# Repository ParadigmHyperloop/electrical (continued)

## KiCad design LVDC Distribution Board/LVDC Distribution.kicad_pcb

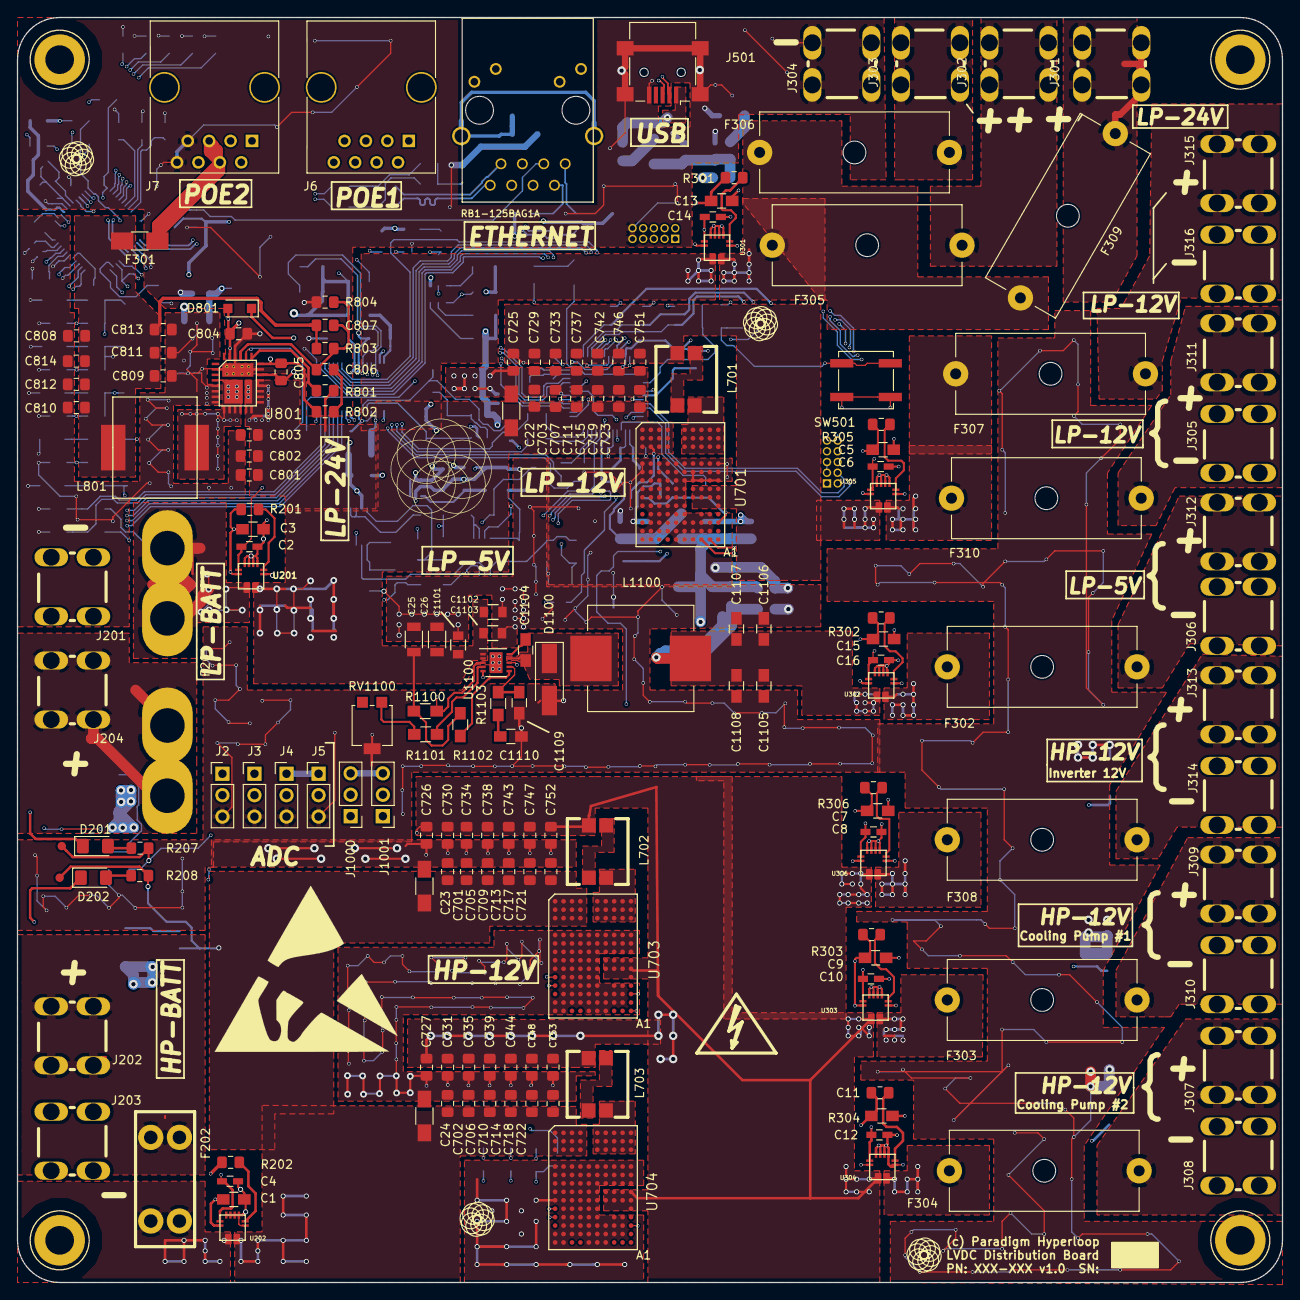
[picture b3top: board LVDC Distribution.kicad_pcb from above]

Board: 4 copper layers, 150.0 x 150.0 mm, 370 parts (0 on the bottom side), 204 nets.

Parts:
C1, C3, C5, C7, C9, C11, C13, C15, C17: 0.1uF; C_0805_HandSoldering
C2, C4, C6, C8, C10, C12, C14, C16: 1nF; C_0603_HandSoldering
C18: 0.1uF; SMD_pkg_0805
C19, C20: 15pF; SMD_pkg_0603
C21: 0.1u; C_0603
C22, C23, C24: 100uF; C_1206_HandSoldering
C25, C26: 10u; SMD_pkg_1206
C27, C709, C710, C711, C713, C714, C715, C717, C718, C719, C721, C722, C723: 4.7uF; C_0805_2012Metric_Pad1.15x1.40mm_HandSolder
C28: 1u; C_0402
C29: 10nF; R_0402
C31, C32, C33, C34, C35, C36: 0.1uF; R_0402
C37, C602: 18pF; R_0402
C501, C504, C506, C609, C801, C808: 10uF; C_0805_2012Metric_Pad1.15x1.40mm_HandSolder
C502, C503, C507, C751, C752, C753, C805, C806: 0.1uF; C_0805_2012Metric_Pad1.15x1.40mm_HandSolder
C505, C510, C741, C742, C743, C744, C746, C747, C748, C750: 1uF; C_0805_2012Metric_Pad1.15x1.40mm_HandSolder
C508, C509: 22pF; SMD_pkg_0603
C605, C606: 6.8nF; C_0805_2012Metric_Pad1.15x1.40mm_HandSolder
C607: 10nF; C_0805_2012Metric_Pad1.15x1.40mm_HandSolder
C608: 100nF; C_0805_2012Metric_Pad1.15x1.40mm_HandSolder
C701, C702, C703, C705, C706, C707, C725, C726, C727, C729, C730, C731, C733, C734, C735, C737, C738, C739, C809, C810, C811, C812, C813, C814: 22uF; C_0805_2012Metric_Pad1.15x1.40mm_HandSolder
C802, C803, C804: 2.2uF; C_0805_2012Metric_Pad1.15x1.40mm_HandSolder
C807: 4.7nF; C_0805_2012Metric_Pad1.15x1.40mm_HandSolder
C900, C903, C904, C906, C907, C1001, C1004: 1u; C_0805_HandSoldering
C901, C1000, C1002, C1003, C1005, C1108: 0.1u; C_0805_HandSoldering
C902, C905: 10u; C_0805_HandSoldering
C908: 150p; C_0805_HandSoldering
C1101: 10u; SMD_pkg_0805
C1102: 0.1u; SMD_pkg_0805
C1103: 10n; SMD_pkg_0805
C1104: 47n; C_0805_HandSoldering
C1105, C1106: 22u; C_0805_HandSoldering
C1107: 18u; C_0805_HandSoldering
C1109: 22p; C_0805_HandSoldering
C1110: 1500p; C_0805_HandSoldering
D201, D202, D701, D702, D703, D704, D705: BLUE; LED_1206_3216Metric_Pad1.42x1.75mm_HandSolder
D501, D502: GREEN; LED_1206_3216Metric_Pad1.42x1.75mm_HandSolder
D801: D_Schottky; D_SOD-123F
D1100: 2A/40V; D_SMA_Handsoldering
F201: 40A; FUSE_MAXI_36-3555-2-ND
F202: 25A; FUSE_MINI_36-3568-ND
F301: 2A; Fuse_SMD1206_HandSoldering
F302: 1A; Fuseholder5x20_horiz_open_Schurter_0031_8201
F303, F304, F307, F308: 3A; Fuseholder5x20_horiz_open_Schurter_0031_8201
F305, F306, F309: 8A; Fuseholder5x20_horiz_open_Schurter_0031_8201
F310: 2A; Fuseholder5x20_horiz_open_Schurter_0031_8201
F501: 500mA; SMD_pkg_0805
H1, H2, H3, H4: Mount; 3.4mm_mounting_hole_SILK
J1: EXT_SPI; PinHeader_2x05_P1.27mm_Vertical
J2, J3, J4, J5: ADC_IN1; PinHeader_1x03_P2.54mm_Vertical
J6, J7: RJ45_LED; RJ45_8
J201: BAT_LP_IN-; LVDC_M3_Lug
J202: BAT_HP_IN+; LVDC_M3_Lug
J203: BAT_HP_IN-; LVDC_M3_Lug
J204: BAT_LP_IN+; LVDC_M3_Lug
J301, J302, J303, J304, J305, J306, J307, J308, J309, J310, J311, J312, J313, J314, J315, J316: Lug Terminal; LVDC_M3_Lug
J501: USB_B_Mini; USB_Mini-B_Lumberg_2486_01_Horizontal
J502: Conn_02x05_Odd_Even; PinHeader_2x05_P1.27mm_Vertical
J601: RB1-125BAG1A; WIZNET_RB1-125BAG1A
J1000, J1001: Conn_01x03_Female; PinHeader_1x03_P2.54mm_Vertical
JP701: Jumper; R_0805_2012Metric_Pad1.15x1.40mm_HandSolder
L501, L502: Ferrite_Bead; R_1206_3216Metric_Pad1.42x1.75mm_HandSolder
L601, L602: Ferrite_Bead_Small; R_1206_3216Metric_Pad1.42x1.75mm_HandSolder
L701, L702, L703: FPT705-230-R; Inductor_Dual_Eaton
L801: 47uH; Wurth_Inductor_47uH
L900, L901: Ferrite_Bead; L_0805_HandSoldering
L1100: 22u; L_Wuerth_WE-PD-Typ-LS_Handsoldering
Q201, Q202: Q_NMOS_GDS; TO-252-2
Q301, Q302, Q303: NMOS_GDS; TO-252-2
R1: 330; SMD_pkg_0805
R5, R1001, R1002, R1004: 150; R_0805_HandSoldering
R7, R8, R9, R10: 0; SMD_pkg_0805
R11, R13: 10k; C_0603
R12: 100k; C_0603
R14, R16, R907, R1003, R1006: 0; R_0805_HandSoldering
R18: 10K; R_0402
R23: 1M; R_0402
R43, R44, R45, R46: 0; C_0603
R201, R202, R301, R302, R303, R304, R305, R306, R804: 1k; R_0805_2012Metric_Pad1.15x1.40mm_HandSolder
R203, R205, R707, R709, R711, R713: 900k; R_0805_2012Metric_Pad1.15x1.40mm_HandSolder
R204, R206, R801: 100k; R_0805_2012Metric_Pad1.15x1.40mm_HandSolder
R207, R208: 2k; R_0805_2012Metric_Pad1.15x1.40mm_HandSolder
R209, R211: 700k; R_0805_2012Metric_Pad1.15x1.40mm_HandSolder
R210, R212: 500k; R_0805_2012Metric_Pad1.15x1.40mm_HandSolder
R501, R603, R604: 330; R_0805_2012Metric_Pad1.15x1.40mm_HandSolder
R502, R803: 10k; R_0805_2012Metric_Pad1.15x1.40mm_HandSolder
R503, R504, R505: 100k; SMD_pkg_0805
R506: 680; R_0805_2012Metric_Pad1.15x1.40mm_HandSolder
R606: 0; R_0805_2012Metric_Pad1.15x1.40mm_HandSolder
R607, R608, R611, R612, R613, R614, R615, R624, R625, R626: 10K; R_0805_2012Metric_Pad1.15x1.40mm_HandSolder
R609, R610, R616, R619: 49.9; R_0805_2012Metric_Pad1.15x1.40mm_HandSolder
R617, R618, R620, R621: 33; R_0805_2012Metric_Pad1.15x1.40mm_HandSolder
R622: 10; R_0805_2012Metric_Pad1.15x1.40mm_HandSolder
R623: 12.4K; R_0805_2012Metric_Pad1.15x1.40mm_HandSolder
R701: 2.5k; R_0805_HandSoldering
R702, R705: 4.7k; R_0805_2012Metric_Pad1.15x1.40mm_HandSolder
R703: 58; R_0805_2012Metric_Pad1.15x1.40mm_HandSolder
R704: 9.2k; R_0805_2012Metric_Pad1.15x1.40mm_HandSolder
R706: 11k; R_0805_2012Metric_Pad1.15x1.40mm_HandSolder
R708, R714: 250k; R_0805_2012Metric_Pad1.15x1.40mm_HandSolder
R710: 620k; R_0805_2012Metric_Pad1.15x1.40mm_HandSolder
R712: 120k; R_0805_2012Metric_Pad1.15x1.40mm_HandSolder
R802: 133k; R_0805_2012Metric_Pad1.15x1.40mm_HandSolder
R900, R909, R910, R1100, R1101, R1102: 10k; R_0805_HandSoldering
R901, R902, R903: 100k; R_0805_HandSoldering
R904: 45k; R_0805_HandSoldering
R905: 5k; R_0805_HandSoldering
R906: 50k; R_0805_HandSoldering
R908: 100; R_0805_HandSoldering
R1000, R1007: 1M; R_0805_HandSoldering
R1103: 24.9k; R_0805_HandSoldering
RV1: R_POT; Potentiometer_Bourns_3314G_Vertical
RV1100: 100k; Potentiometer_Bourns_3314G_Vertical
SW501: SW_Push; SW_SPST_B3SL-1022P
TP1, TP2, TP3, TP4, TP5, TP6, TP7, TP601, TP604, TP605, TP606, TP607, TP608: Conn_01x01; Testpoint_circle_0.5mm
U1: W5500; LQFP-48_7x7mm_Pitch0.5mm
U201, U202, U301, U302, U303, U304, U305, U306: ACS711
U501: ATSAMD21G18A-MFT; TQFP-48_7x7mm_Pitch0.5mm
U701, U703, U704: PI3303-00-LGIZ; PI330X
U705: AZ1117-3.3; SOT-223-3_TabPin2
U801: MIC28510; MIC28510_QFN
U900: LM3880; SOT-23-6
U901: LM4132; SOT-23-5_HandSoldering
U902: ADS7953; TSSOP-38_4.4x9.7mm_Pitch0.5mm
U903: LMV601; SOT-363_SC-70-6
U904: OPA192; SOT-23-5_HandSoldering
U1000, U1001: AD849X; MSOP-8_3x3mm_Pitch0.65mm
U1100: A8591; DFN-10-1EP_3x3mm_Pitch0.5mm
Y1, Y601: 25MHz; Murata_25MHz_XTAL_XRCGB25M000F3M00R0
Y501: 32.7680kHz; Crystal_SMD_EuroQuartz_EQ161-2Pin_3.2x1.5mm_HandSoldering
lo1, lo1#2: Serial Block; SN_BLOCK
lo2, lo4, lo8: Logo; ParadigmLogo_0_5x0_5
lo3, lo3#2, lo10, lo11, lo12, lo13: Logo; Paradigm_Logo_Very_Small
lo5: Logo; Symbol_HighVoltage_Type2_SilkTop_VerySmall
lo6: Logo; KiCad-Logo_40mm_SilkScreen
lo7, lo9: Logo; ESD-Logo_22x20mm_SilkScreen

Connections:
3V3A_W5500: C31.1, C32.1, C33.1, C34.1, C35.1, C36.1, C609.1, J601.L1, J601.L3, L602.2, R606.2, R607.2, R608.2, R609.1, R610.1, R622.2, TP608.1, U1.28, U1.32, U1.35, U1.39, U1.41, U1.45
3V3_FILT: C506.1, C507.1, L502.1, U501.6
+3V3: C1.1, C3.1, C5.1, C7.1, C9.1, C11.1, C13.1, C15.1, C501.1, C502.1, C503.1, C750.1, C905.1, J502.1, L502.2, L602.1, L901.2, R201.2, R202.2, R301.2, R302.2, R303.2, R304.2, R305.2, R306.2, R502.1, R506.2, R703.2, R909.2, R910.2, TP3.1, U201.12, U202.12, U301.12, U302.12, U303.12, U304.12, U305.12, U306.12, U501.17, U501.36, U501.44, U705.2
+5V: C28.1, C741.1, C804.1, C900.1, C902.1, C907.2, C1105.1, C1106.1, C1107.1, C1108.1, D801.2, J1.1, J1.2, J2.1, J3.1, J4.1, J5.1, J1000.3, J1001.3, JP701.2, L900.2, L1100.2, R704.1, R709.1, R900.1, R901.1, R902.1, R903.1, R904.1, R906.2, TP2.1, U302.1, U705.3, U801.1, U900.1, U901.4, U903.5, U903.6, U904.5, U1000.7, U1001.7, U1100.5
/Inputs and Fusing/HP_Vin+: C23.1, C24.1, C701.1, C702.1, C705.1, C706.1, C709.1, C710.1, C713.1, C714.1, C717.1, C718.1, C721.1, C722.1, R208.2, R209.1, TP7.1, U202.3, U703.1, U704.1
/Inputs and Fusing/LP_Vin+: C22.1, C25.1, C26.1, C703.1, C707.1, C711.1, C715.1, C719.1, C723.1, C801.1, C802.1, C803.1, C1101.1, C1102.1, C1103.1, R11.1, R207.2, R211.1, R801.1, R1100.1, R1102.1, TP6.1, U201.3, U301.1, U701.1, U801.4, U1100.1, U1100.2
/Power Conversion/5V_Converter/COMP: C1109.1, R1103.1, U1100.7
/Power Conversion/HP12V: C726.1, C727.1, C730.1, C731.1, C734.1, C735.1, C738.1, C739.1, C743.1, C744.1, C747.1, C748.1, C752.1, C753.1, L702.3, L703.3, R705.1, R713.1, TP5.1, U303.1, U304.1, U306.1, U703.11, U703.12, U704.11, U704.12
/Power Conversion/LP12V: C725.1, C729.1, C733.1, C737.1, C742.1, C746.1, C751.1, L701.3, R702.1, R707.1, TP1.1, U305.1, U701.11, U701.12
/Power Conversion/LP24V: C807.2, C808.1, C809.1, C810.1, C811.1, C812.1, C813.1, C814.1, F301.2, L801.2, R706.1, R711.1, R803.2, TP4.1
/Power Conversion/USB5V: C504.1, C505.1, JP701.1, L501.1, R501.1
/Power Outputs/NAP_PoE/NAP_Vin+: F301.1, J7.4, J7.5
/Power Outputs/NAP_PoE/RX+: J6.1, J7.1
/Power Outputs/NAP_PoE/RX-: J6.2, J7.2
/Power Outputs/NAP_PoE/TX+: J6.3, J7.3
/Power Outputs/NAP_PoE/TX-: J6.6, J7.6
/SAMD21uC/ADC_CS: R7.1, U501.9
/SAMD21uC/ADC_SCLK: R8.1, U501.10
/SAMD21uC/ADC_SDI: R9.1, U501.11
/SAMD21uC/ADC_SDO: R10.1, U501.12
/SAMD21uC/ADC_Sensors/2V5_VREF: C901.1, U901.5
/SAMD21uC/ADC_Sensors/3V3_EN: R902.2, U900.5
/SAMD21uC/ADC_Sensors/3V3_FILT: C906.1, L901.1, U902.36
/SAMD21uC/ADC_Sensors/5V_FILT: C903.1, C904.1, L900.1, U902.5, U902.29
/SAMD21uC/ADC_Sensors/AINP: C908.1, R908.1, U902.8
/SAMD21uC/ADC_Sensors/MXO: R906.1, R907.2, U902.7, U904.3
/SAMD21uC/ADC_Sensors/TC_VREF: U903.3, U903.4
/SAMD21uC/ADC_Sensors/Thermocouple/OUT1: R1003.1, U1000.5, U1000.6
/SAMD21uC/ADC_Sensors/Thermocouple/OUT2: R1006.1, U1001.5, U1001.6
/SAMD21uC/ADC_Sensors/Thermocouple/TC_VREF: U1000.2, U1001.2
/SAMD21uC/ADC_Sensors/VREF_EN: R903.2, U900.4, U901.3
/SAMD21uC/AIN_0: J2.2, U501.8
/SAMD21uC/AIN_1: J3.2, U501.7
/SAMD21uC/AIN_2: J4.2, U501.48
/SAMD21uC/AIN_3: J5.2, U501.47
/SAMD21uC/EXT_SPI_CS0: J1.4, U501.13
/SAMD21uC/EXT_SPI_CS1: J1.6, U501.14
/SAMD21uC/EXT_SPI_SCLK: J1.7, U501.30
/SAMD21uC/EXT_SPI_SDI: J1.3, U501.28
/SAMD21uC/EXT_SPI_SDO: J1.5, U501.29
/SAMD21uC/~RESET: C18.1, R1.1, U501.40
/Wiznet Ethernet/1V2_VBG_NC: TP607.1, U1.42
/Wiznet Ethernet/1V20: C29.1, U1.46
/Wiznet Ethernet/3V3D_W5500: R606.1, U1.4
/Wiznet Ethernet/ACT_LED: R604.2, U1.3
/Wiznet Ethernet/ACT_LED_R: J601.L4, R604.1
/Wiznet Ethernet/DUP_LED_NC: TP601.1, U1.2
/Wiznet Ethernet/LINK_LED: R603.1, U1.1
/Wiznet Ethernet/LINK_LED_R: J601.L2, R603.2
/Wiznet Ethernet/PMODE0: R624.2, U1.21
/Wiznet Ethernet/PMODE1: R625.2, U1.20
/Wiznet Ethernet/PMODE2: R626.2, U1.19
/Wiznet Ethernet/REF_CAP: C27.1, U1.44
/Wiznet Ethernet/REF_RES: R623.2, U1.34
/Wiznet Ethernet/RSVD0: R18.2, U1.47
/Wiznet Ethernet/RSVD1: R611.1, U1.14
/Wiznet Ethernet/RSVD2: R612.1, U1.15
/Wiznet Ethernet/RSVD3: R613.1, U1.16
/Wiznet Ethernet/RSVD4: R614.1, U1.17
/Wiznet Ethernet/RSVD5: R615.1, U1.18
/Wiznet Ethernet/RX_C_N: C606.2, J601.R8
/Wiznet Ethernet/RX_C_P: C605.2, J601.R7
/Wiznet Ethernet/RX_N: R621.2, U1.29
/Wiznet Ethernet/RX_P: R620.2, U1.30
/Wiznet Ethernet/SPD_LED_NC: TP606.1, U1.48
/Wiznet Ethernet/TCT_RCT: C608.1, J601.R3, R622.1
/Wiznet Ethernet/TX_N: R618.2, U1.25
/Wiznet Ethernet/TX_P: R617.2, U1.26
/Wiznet Ethernet/TX_R_N: J601.R2, R610.2, R618.1
/Wiznet Ethernet/TX_R_P: J601.R1, R609.2, R617.1
/Wiznet Ethernet/XTAL_IN: C37.2, R23.2, U1.6, Y601.2
/Wiznet Ethernet/XTAL_OUT: C602.2, R23.1, U1.7, Y601.1
ADC_S0_BUS: R7.2, R909.1, U902.31
ADC_S1_BUS: R8.2, U902.32
ADC_S2_BUS: R9.2, U902.33
ADC_S3_BUS: R10.2, R910.1, U902.34
COOL_PUMP_CTRL_1: Q303.1, R504.1, U501.26
COOL_PUMP_CTRL_2: Q301.1, R503.1, U501.27
CoolingP1_Current: C10.1, U303.11, U902.25
CoolingP2_Current: C12.1, U304.11, U902.26
GND: C1.2, C2.2, C3.2, C4.2, C5.2, C6.2, C7.2, C8.2, C9.2, C10.2, C11.2, C12.2, C13.2, C14.2, C15.2, C16.2, C17.2, C18.2, C19.1, C20.1, C21.2, C22.2, C23.2, C24.2, C25.2, C26.2, C27.2, C28.2, C29.2, C31.2, C32.2, C33.2, C34.2, C35.2, C36.2, C37.1, C501.2, C502.2, C503.2, C504.2, C505.2, C506.2, C507.2, C508.2, C509.2, C510.2, C602.1, C607.2, C608.2, C609.2, C701.2, C702.2, C703.2, C705.2, C706.2, C707.2, C709.2, C710.2, C711.2, C713.2, C714.2, C715.2, C717.2, C718.2, C719.2, C721.2, C722.2, C723.2, C725.2, C726.2, C727.2, C729.2, C730.2, C731.2, C733.2, C734.2, C735.2, C737.2, C738.2, C739.2, C741.2, C742.2, C743.2, C744.2, C746.2, C747.2, C748.2, C750.2, C751.2, C752.2, C753.2, C801.2, C802.2, C803.2, C804.2, C808.2, C809.2, C810.2, C811.2, C812.2, C813.2, C814.2, C900.2, C901.2, C902.2, C903.2, C904.2, C905.2, C906.2, C907.1, C908.2, C1000.1, C1002.2, C1003.1, C1005.2, C1101.2, C1102.2, C1103.2, C1105.2, C1106.2, C1107.2, C1108.2, C1109.2, C1110.2, D501.1, D701.1, D702.1, D703.1, D704.1, D705.1, D1100.2, J1.9, J1.10, J2.3, J3.3, J4.3, J5.3, J7.7, J7.8, J304.1, J306.1, J312.1, J316.1, J501.5, J501.6, J502.3, J502.5, L601.1, Q201.3, Q202.3, Q301.3, Q302.3, Q303.3, R13.2, R18.1, R204.2, R206.2, R210.1, R212.1, R503.2, R504.2, R505.2, R611.2, R612.2, R613.2, R614.2, R615.2, R623.1, R624.1, R625.1, R626.1, R708.2, R710.2, R712.2, R714.2, R804.2, R905.2, R1000.2, R1007.2, RV1.2, RV1100.2, SW501.1, U1.5, U1.24, U1.27, U1.33, U1.38, U1.40, U1.43, U201.5, U201.7, U202.5, U202.7, U301.5, U301.7, U302.5, U302.7, U303.5, U303.7, U304.5, U304.7, U305.5, U305.7, U306.5, U306.7, U501.5, U501.18, U501.35, U501.42, U701.3, U701.6, U701.7, U703.6, U703.7, U704.6, U704.7, U705.1, U801.2, U801.5, U900.2, U901.2, U902.3, U902.6, U902.9, U902.10, U902.19, U902.20, U902.30, U902.35, U903.2, U904.2, U1000.3, U1001.3, U1100.8
HP12V_EN: R44.2, U501.19
HP12V_VSense: R713.2, R714.1, U902.13
HPBAT_VSense: R205.2, R206.1, U902.17
HPBAT_Voltage: F202.1, R205.1, U202.1
HPBatt_Current: C4.1, U202.11, U902.11
INVERTER_CTRL: Q302.1, R505.1, U501.25
Inverter12V_Current: C8.1, U306.11, U902.22
LP5V_EN: R46.2, U501.4
LP5V_Output_Current: C16.1, U302.11, U902.24
LP5V_VSense: R709.2, R710.1, U902.16
LP12V_EN: R43.2, U501.3
LP12V_Output_Current: C6.1, U305.11, U902.21
LP12V_VSense: R707.2, R708.1, U902.15
LP24V_EN: R45.2, U501.20
LP24V_VSense: R711.2, R712.1, U902.14
LPBAT_VSense: R203.2, R204.1, U902.18
LPBAT_Voltage: F201.1, R203.1, U201.1
LPBatt_Current: C2.1, U201.11, U902.12
NETW_CS: U1.8, U501.21
NETW_INT_L: R608.1, TP605.1, U1.12, U501.31
NETW_MISO: U1.10, U501.22
NETW_MOSI: U1.11, U501.15
NETW_RESET_L: R607.1, TP604.1, U1.13, U501.32
NETW_SCLK: U1.9, U501.16
unnamed: C17.1, C510.1, U501.43
unnamed: C19.2, U501.23, Y1.2
unnamed: C20.2, U501.24, Y1.1
unnamed: C21.1, U701.8
unnamed: C508.1, U501.1, Y501.1
unnamed: C509.1, U501.2, Y501.2
unnamed: C605.1, R619.1, R620.1
unnamed: C606.1, R616.1, R621.1
unnamed: C607.1, R616.2, R619.2
unnamed: C805.1, L801.1, R802.2, U801.8, U801.9
unnamed: C805.2, D801.1, U801.7
unnamed: C806.1, C807.1, R803.1, R804.1, U801.10
unnamed: C806.2, R802.1
unnamed: C1000.2, C1001.1, R1001.1, U1000.1
unnamed: C1001.2, C1002.1, R1002.1, U1000.8
unnamed: C1003.2, C1004.1, R1004.1, U1001.1
unnamed: C1004.2, C1005.1, R5.1, U1001.8
unnamed: C1104.1, D1100.1, L1100.1, U1100.9
unnamed: C1104.2, U1100.10
unnamed: C1110.1, R1103.2
unnamed: D201.1, J201.1, Q202.2
unnamed: D201.2, R207.1
unnamed: D202.1, J203.1, Q201.2
unnamed: D202.2, R208.1
unnamed: D501.2, R501.2
unnamed: D502.1, U501.38
unnamed: D502.2, R506.1
unnamed: D701.2, R702.2
unnamed: D702.2, R703.1
unnamed: D703.2, R704.2
unnamed: D704.2, R705.2
unnamed: D705.2, R706.2
unnamed: F201.2, J204.1
unnamed: F202.2, J202.1
unnamed: F302.1, J305.1
unnamed: F302.2, U302.3
unnamed: F303.1, J309.1
unnamed: F303.2, U303.3
unnamed: F304.1, J307.1
unnamed: F304.2, U304.3
unnamed: F305.1, J302.1
unnamed: F305.2, F306.2, F309.2, U301.3
unnamed: F306.1, J303.1
unnamed: F307.1, J315.1
unnamed: F307.2, F310.2, U305.3
unnamed: F308.1, J313.1
unnamed: F308.2, U306.3
unnamed: F309.1, J301.1
unnamed: F310.1, J311.1
unnamed: F501.1, L501.2
unnamed: F501.2, J501.1
unnamed: J308.1, Q301.2
unnamed: J310.1, Q303.2
unnamed: J314.1, Q302.2
unnamed: J601.SH, L601.2
unnamed: J1000.1, R1002.2, R1003.2
unnamed: J1000.2, R1000.1, R1001.2
unnamed: J1001.1, R5.2, R1006.2
unnamed: J1001.2, R1004.2, R1007.1
unnamed: L701.1, U701.13
unnamed: L701.2, L701.4
unnamed: L702.1, U703.13
unnamed: L702.2, L702.4
unnamed: L703.1, U704.13
unnamed: L703.2, L703.4
unnamed: Q201.1, R209.2, R210.2
unnamed: Q202.1, R211.2, R212.2
unnamed: R11.2, R13.1, R43.1, U701.5
unnamed: R12.2, RV1.3, U701.9
unnamed: R14.1, U703.2
unnamed: R14.2, U704.3
unnamed: R16.1, U703.5
unnamed: R16.2, R44.1, U704.5
unnamed: R45.1, U801.6
unnamed: R201.1, U201.6
unnamed: R202.1, U202.6
unnamed: R301.1, U301.6
unnamed: R302.1, U302.6
unnamed: R303.1, U303.6
unnamed: R304.1, U304.6
unnamed: R305.1, U305.6
unnamed: R306.1, U306.6
unnamed: R701.1, U703.3, U703.4
unnamed: R701.2, U704.2
unnamed: R801.2, U801.3
unnamed: R900.2, U900.3
unnamed: R901.2, U900.6
unnamed: R904.2, R905.1, U903.1
unnamed: R907.1, R908.2, U904.1, U904.4
unnamed: R46.1, R1100.2, U1100.3
unnamed: R1101.1, U1100.4
unnamed: R1101.2, RV1100.1
unnamed: R1102.2, U1100.6
Nodes_Current: C14.1, U301.11, U902.23
SWCLK: J502.4, U501.45
SWDIO: J502.2, U501.46
USB+: J501.3, U501.34
USB-: J501.2, U501.33
~RESET~: J502.10, R1.2, R502.2, SW501.2

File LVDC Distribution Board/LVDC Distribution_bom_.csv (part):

Component,Description,Part,References,Value,Footprint,Quantity Per PCB,Datasheet,Mfg. Part Num,Package,Mfg. Name,MP,Tolerance,Vendor Part Num,Category,Status,Family,MPN,Digi-Key_PN,DK_Datasheet_Link,DK_Detail_Page,Manufacturer
1,"Unpolarized capacitor, small symbol",C_Small,C21 C1102,0.1u,,2,~,,,,,,,,,,,,,,
2,Unpolarized capacitor,C,C1 C3 C5 C7 C9 C11 C15 C901 C1000 C1002 C1003 C1005 C1108,0.1uF,C_0805_HandSoldering,13,~,,,,,,,,,,,,,,
3,Unpolarized capacitor,C,C13 C17 C18 C502 C503 C507 C608 C610 C611 C612 C613 C614 C615 C751 C752 C753 C805 C806,0.1uF,C_0805_2012Metric_Pad1.15x1.40mm_HandSolder,18,~,,,,,,,,,,,,,,
4,Unpolarized capacitor,C,C22 C23 C24,100uF,C_1206_HandSoldering,3,445-11739-1-ND,,,,,,,,,,,,,,
5,"Unpolarized capacitor, small symbol",C_Small,C1103,10n,,1,~,,,,,,,,,,,,,,
6,Unpolarized capacitor,C,C604 C607,10nF,C_0805_2012Metric_Pad1.15x1.40mm_HandSolder,2,,,,,,,,,,,,,,,
7,"Unpolarized capacitor, small symbol",C_Small,C1101,10u,,1,~,,,,,,,,,,,,,,
8,Unpolarized capacitor,C,C902 C905,10u,C_0805_HandSoldering,2,~,,,,,,,,,,,,,,
9,Unpolarized capacitor,C,C501 C504 C506 C609 C801 C808,10uF,C_0805_2012Metric_Pad1.15x1.40mm_HandSolder,6,~,,,,,,,,,,,,,,
10,"Unpolarized capacitor, small symbol",C_Small,C1110,1500p,C_0805_HandSoldering,1,~,,,,,,,,,,,,,,
11,Unpolarized capacitor,C,C908,150p,C_0805_HandSoldering,1,~,,,,,,,,,,,,,,
12,Unpolarized capacitor,C,C19 C20,15pF,C_0805_2012Metric_Pad1.15x1.40mm_HandSolder,2,~,,,,,,,,,,,,,,
13,Unpolarized capacitor,C,C601 C602,18pF,C_0805_2012Metric_Pad1.15x1.40mm_HandSolder,2,,,,,,,,,,,,,,,
14,"Unpolarized capacitor, small symbol",C_Small,C1107,18u,C_0805_HandSoldering,1,~,,,,,,,,,,,,,,
15,Unpolarized capacitor,C,C2 C4 C6 C8 C10 C12 C14 C16,1nF,C_0603_HandSoldering,8,~,,,,,,,,,,,,,,
16,Unpolarized capacitor,C,C900 C903 C904 C906 C907 C1001 C1004,1u,C_0805_HandSoldering,7,~,,,,,,,,,,,,,,
17,Unpolarized capacitor,C,C505 C510 C741 C742 C743 C744 C746 C747 C748 C750,1uF,C_0805_2012Metric_Pad1.15x1.40mm_HandSolder,10,~,,,,,,,,,,,,,,
18,Unpolarized capacitor,C,C802 C803 C804,2.2uF,C_0805_2012Metric_Pad1.15x1.40mm_HandSolder,3,~,,,,,,,,,,,,,,
19,"Unpolarized capacitor, small symbol",C_Small,C1109,22p,C_0805_HandSoldering,1,~,,,,,,,,,,,,,,
20,Unpolarized capacitor,C,C508 C509,22pF,C_0805_2012Metric_Pad1.15x1.40mm_HandSolder,2,~,,,,,,,,,,,,,,
21,"Unpolarized capacitor, small symbol",C_Small,C1105 C1106,22u,C_0805_HandSoldering,2,~,,,,,,,,,,,,,,
22,Unpolarized capacitor,C,C701 C702 C703 C705 C706 C707 C725 C726 C727 C729 C730 C731 C733 C734 C735 C737 C738 C739 C809 C810 C811 C812 C813 C814,22uF,C_0805_2012Metric_Pad1.15x1.40mm_HandSolder,24,445-11739-1-ND,,,,,,,,,,,,,,
23,Unpolarized capacitor,C,C807,4.7nF,C_0805_2012Metric_Pad1.15x1.40mm_HandSolder,1,~,,,,,,,,,,,,,,
24,Unpolarized capacitor,C,C603 C709 C710 C711 C713 C714 C715 C717 C718 C719 C721 C722 C723,4.7uF,C_0805_2012Metric_Pad1.15x1.40mm_HandSolder,13,,,,,,,,,,,,,,,
25,"Unpolarized capacitor, small symbol",C_Small,C1104,47n,C_0805_HandSoldering,1,~,,,,,,,,,,,,,,
26,Unpolarized capacitor,C,C605 C606,6.8nF,C_0805_2012Metric_Pad1.15x1.40mm_HandSolder,2,,,,,,,,,,,,,,,
27,Diode,D,D1100,2A/40V,,1,641-1698-1-ND,,,,,,,,,,,,,,
28,Light emitting diode,LED,D201 D202 D701 D702 D703 D704 D705,BLUE,LED_1206_3216Metric_Pad1.42x1.75mm_HandSolder,7,~,,,,,,,,,,,,,,
29,"Schottky diode, filled shape",D_Schottky_ALT,D801,D_Schottky,D_SOD-123F,1,~,,,,,,,,,,,,,,
30,Light emitting diode,LED,D501 D502,GREEN,LED_1206_3216Metric_Pad1.42x1.75mm_HandSolder,2,~,,,,,,,,,,,,,,
31,Fuse,Fuse,F302,1A,Fuse_clip_Littelfuse_5x20mm,1,~,,,,,,,,,,,,,,
32,Fuse,Fuse,F202,25A,Fuse_clip_Littelfuse_5x20mm,1,~,,,,,,,,,,,,,,
33,Fuse,Fuse,F301 F310,2A,Fuse_clip_Littelfuse_5x20mm,2,~,,,,,,,,,,,,,,
34,Fuse,Fuse,F303 F304 F307 F308,3A,Fuse_clip_Littelfuse_5x20mm,4,~,,,,,,,,,,,,,,
35,Fuse,Fuse,F201,40A,Fuse_clip_Littelfuse_5x20mm,1,~,,,,,,,,,,,,,,
36,Fuse,Fuse,F501,500mA,Fuse_clip_Littelfuse_5x20mm,1,~,,,,,,,,,,,,,,
37,Fuse,Fuse,F305 F306 F309,8A,Fuse_clip_Littelfuse_5x20mm,3,~,,,,,,,,,,,,,,
38,"Generic connector, single row, 01x03, script generated (kicad-library-utils/schlib/autogen/connector/)",Conn_01x03_Female,J2 J3 J4 J5,ADC_IN1,,4,A19470-ND,,,,,,,,,,,,,,
39,"Generic screw terminal, single row, 01x01, script generated (kicad-library-utils/schlib/autogen/connector/)",Screw_Terminal_01x01,J202,BAT_HP_IN+,Screw_mount_Keystone,1,~,,,,,,,,,,,,,,
40,"Generic screw terminal, single row, 01x01, script generated (kicad-library-utils/schlib/autogen/connector/)",Screw_Terminal_01x01,J203,BAT_HP_IN-,Screw_mount_Keystone,1,~,,,,,,,,,,,,,,
41,"Generic screw terminal, single row, 01x01, script generated (kicad-library-utils/schlib/autogen/connector/)",Screw_Terminal_01x01,J204,BAT_LP_IN+,Screw_mount_Keystone,1,~,,,,,,,,,,,,,,
42,"Generic screw terminal, single row, 01x01, script generated (kicad-library-utils/schlib/autogen/connector/)",Screw_Terminal_01x01,J201,BAT_LP_IN-,Screw_mount_Keystone,1,~,,,,,,,,,,,,,,
43,"Generic connector, single row, 01x03, script generated (kicad-library-utils/schlib/autogen/connector/)",Conn_01x03_Female,J1000 J1001,Conn_01x03_Female,,2,~,,,,,,,,,,,,,,
44,"Generic connector, double row, 02x05, odd/even pin numbering scheme (row 1 odd numbers, row 2 even numbers), script generated (kicad-library-utils/schlib/autogen/connector/)",Conn_02x05_Odd_Even,J502,Conn_02x05_Odd_Even,PinHeader_2x05_P1.27mm_Vertical,1,~,,,,,,,,,,,,,,
45,"Generic connector, double row, 02x05, odd/even pin numbering scheme (row 1 odd numbers, row 2 even numbers), script generated (kicad-library-utils/schlib/autogen/connector/)",Conn_02x05_Odd_Even,J1,EXT_SPI,,1,~,,,,,,,,,,,,,,
46,"Generic screw terminal, single row, 01x01, script generated (kicad-library-utils/schlib/autogen/connector/)",Screw_Terminal_01x01,J301 J302 J303 J304 J305 J306 J307 J308 J309 J310 J311 J312 J313 J314 J315 J316,Lug Terminal,Screw_mount_Keystone,16,~,,,,,,,,,,,,,,
47,,RB1-125BAG1A,J601,RB1-125BAG1A,WIZNET_RB1-125BAG1A,1,2.18 USD,RB1-125BAG1A,HVQFN-36 NXP Semiconductors,WIZnet,RB1-125BAG1A,,,,,,,,,,
48,USB Micro Type B connector,USB_B_Mini,J501,USB_B_Mini,USB_Mini-B_Lumberg_2486_01_Horizontal,1,~,,,,,,,,,,,,,,
49,"Jumper, normally closed",Jumper,JP701,Jumper,R_0805_2012Metric_Pad1.15x1.40mm_HandSolder,1,~,,,,,,,,,,,,,,
50,Inductor,L,L1100,22u,L_Wuerth_WE-PD-Typ-LS_Handsoldering,1,732-1227-1-ND,,,,,,,,,,,,,,
51,Inductor,L,L801,47uH,Wurth_Inductor_47uH,1,~,,,,,,,,,,,,,,
52,Coupled inductor with ferrite core,L_Core_Ferrite_Coupled,L701 L702 L703,FPT705-230-R,Inductor_Dual_Eaton,3,283-4147-1-ND,,,,,,,,,,,,,,
53,Ferrite bead,Ferrite_Bead,L501 L502,Ferrite_Bead,R_1206_3216Metric_Pad1.42x1.75mm_HandSolder,2,~,,,,,,,,,,,,,,
54,Ferrite bead,Ferrite_Bead,L900 L901,Ferrite_Bead,L_0805_HandSoldering,2,~,,,,,,,,,,,,,,
55,"Ferrite bead, small symbol",Ferrite_Bead_Small,L601 L602,Ferrite_Bead_Small,R_1206_3216Metric_Pad1.42x1.75mm_HandSolder,2,,,,,,,,,,,,,,,
56,"N-MOSFET transistor, gate/drain/source",Q_NMOS_GDS,Q301 Q302 Q303,NMOS_GDS,VSONP8_custom,3,~,,,,,,,,,,,,,,
57,"N-MOSFET transistor, gate/drain/source",Q_NMOS_GDS,Q201 Q202,Q_NMOS_GDS,VSONP8_custom,2,DMTH6004SK3-13DICT-ND,,,,,,,,,,,,,,
58,"Resistor, US symbol",R_US,R7 R8 R9 R10 R15 R16 R17 R602 R606,0,R_0805_2012Metric_Pad1.15x1.40mm_HandSolder,9,~,,,,,,,,,,,,,,
59,"Resistor, US symbol",R_US,R14 R907 R1003 R1006,0,R_0805_HandSoldering,4,~,,,,,,,,,,,,,,
60,"Resistor, US symbol",R_US,R622,10,R_0805_2012Metric_Pad1.15x1.40mm_HandSolder,1,,,,,,1%,,,,,,,,,
61,"Resistor, US symbol",R_US,R908,100,R_0805_HandSoldering,1,~,,,,,,,,,,,,,,
62,"Resistor, US symbol",R_US,R12,100k,,1,~,,,,,,,,,,,,,,
63,"Resistor, US symbol",R_US,R204 R206 R503 R504 R505 R801,100k,R_0805_2012Metric_Pad1.15x1.40mm_HandSolder,6,~,,,,,,,,,,,,,,
64,"Resistor, US symbol",R_US,R901 R902 R903,100k,R_0805_HandSoldering,3,~,,,,,,,,,,,,,,
65,"Resistor, US symbol",R_US,R11 R13,10k,,2,~,,,,,,,,,,,,,,
66,Resistor,R,R1100 R1101 R1102,10k,R_0805_HandSoldering,3,~,,,,,,,,,,,,,,
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
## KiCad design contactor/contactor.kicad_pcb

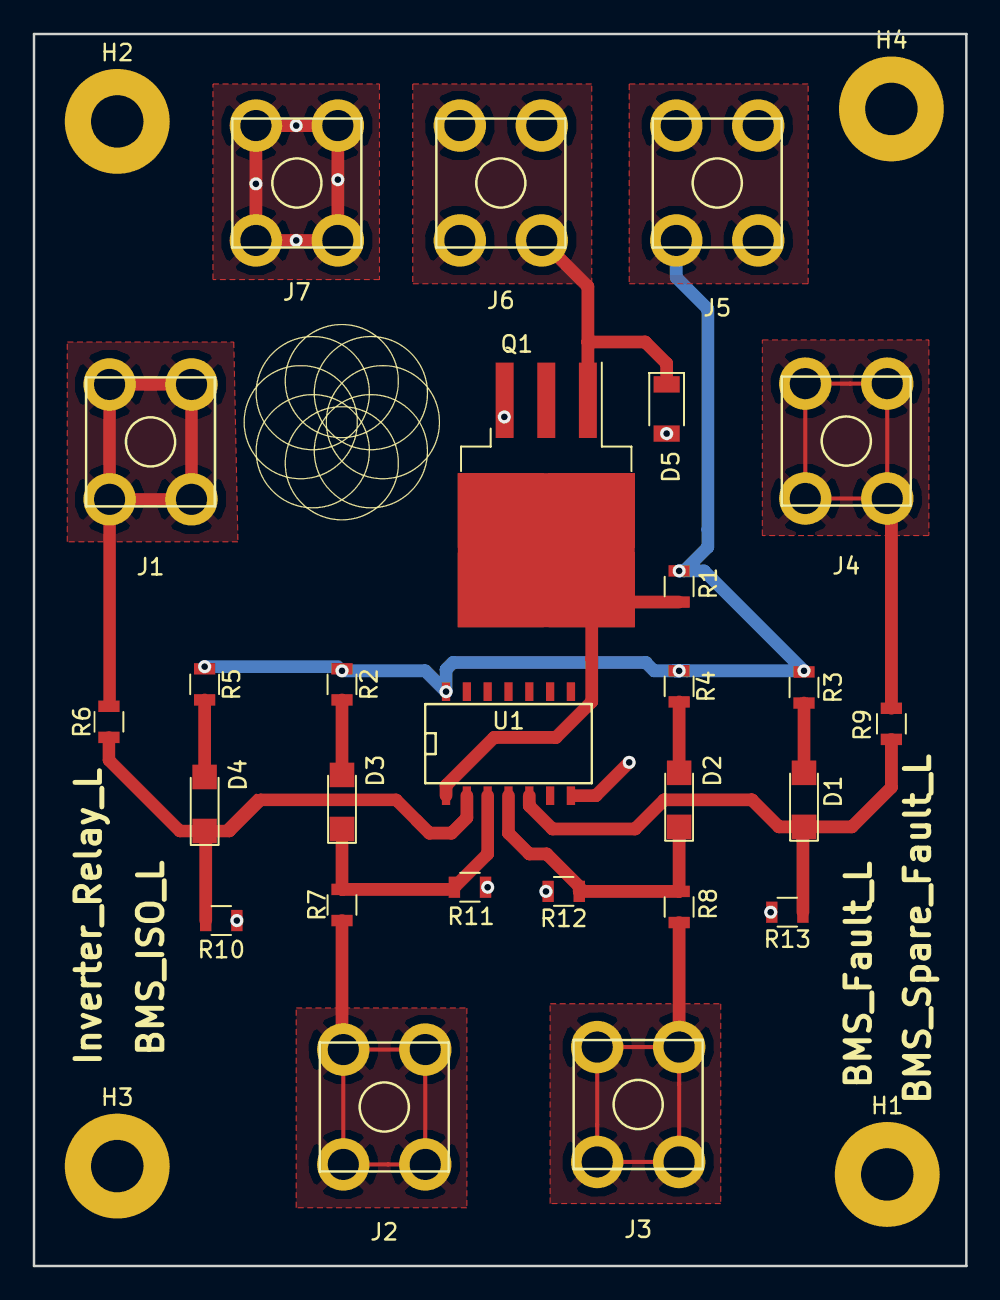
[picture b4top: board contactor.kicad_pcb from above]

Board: 2 copper layers, 56.9 x 75.2 mm, 31 parts (0 on the bottom side), 16 nets.

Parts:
D1, D2, D3, D4: LED; LED_1206
D5: D; D_1206
H1, H2, H3, H4: MountingHole_Pad; MountingHole_3.2mm_M3_Pad
J1, J2, J3, J4, J5, J6, J7: Screw_Terminal_01x01; RingTerminal
Q1: Q_NMOS_DGS; TO-263-3_TabPin2
R1, R2, R3, R4, R5, R6, R7, R8, R9, R10, R11, R12, R13: 10k; R_0805
U1: 74LS21; SOIC-14_N

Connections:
+12V: J5.1, R1.2, R2.1, R3.1, R4.1, R5.1, U1.14
/BMS_Fault_L: D2.1, R8.1, R12.1, U1.4
/BMS_ISO_L: D3.1, R7.1, R11.1, U1.3
/BMS_Spare_Fault_L: D1.1, R9.1, R13.1, U1.5
/Inverter_Relay_L: D4.1, R6.1, R10.1, U1.2
Contactor-: D5.1, J6.1, Q1.1
GND: D5.2, H1.1, H2.1, H3.1, H4.1, J7.1, Q1.3, R10.2, R11.2, R12.2, R13.2, U1.7
unnamed: D1.2, R3.2
unnamed: D2.2, R4.2
unnamed: D3.2, R2.2
unnamed: D4.2, R5.2
unnamed: J1.1, R6.2
unnamed: J2.1, R7.2
unnamed: J3.1, R8.2
unnamed: J4.1, R9.2
unnamed: Q1.2, R1.1, U1.1

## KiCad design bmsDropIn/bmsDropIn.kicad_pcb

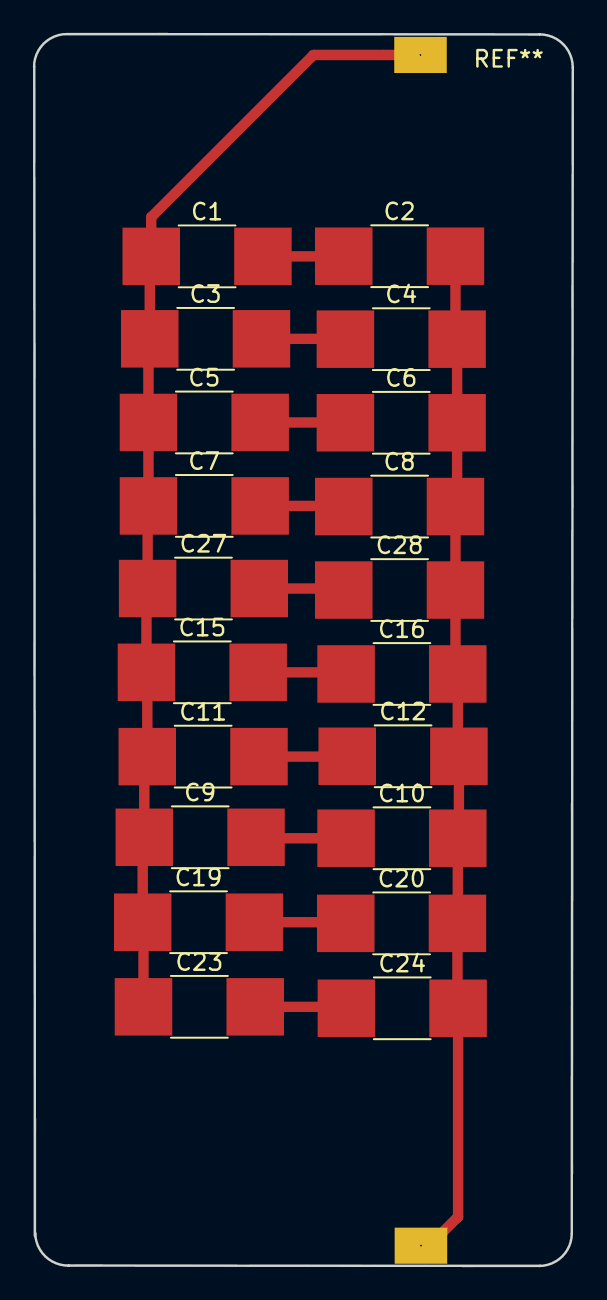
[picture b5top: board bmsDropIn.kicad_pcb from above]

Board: 2 copper layers, 32.8 x 75.0 mm, 20 parts (0 on the bottom side), 12 nets.

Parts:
C1, C2, C3, C4, C5, C6, C7, C8, C9, C10, C11, C12, C15, C16, C19, C20, C23, C24, C27, C28: 0.1u; R_1812_HandSoldering

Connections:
GND: C2.2, C4.2, C6.2, C8.2, C10.2, C12.2, C16.2, C20.2, C24.2, C28.2
unnamed: C1.2, C2.1
unnamed: C3.2, C4.1
unnamed: C5.2, C6.1
unnamed: C7.2, C8.1
unnamed: C9.2, C10.1
unnamed: C11.2, C12.1
unnamed: C15.2, C16.1
unnamed: C19.2, C20.1
unnamed: C23.2, C24.1
unnamed: C27.2, C28.1
VCC: C1.1, C3.1, C5.1, C7.1, C9.1, C11.1, C15.1, C19.1, C23.1, C27.1
